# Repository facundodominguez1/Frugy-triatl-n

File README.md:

# Robot Triatlon "FRUGY" - Bonaerenses 2025

## Frugy 

Este proyecto robot triatlón fue creado con la intencion de competir en las Bonaerenses 21/08/2025. Que fue llevado por los alumnos de 5°6 Ulises Basabe, Facundo Dominguez, Gonzalo Flores y Ramiro Trejo. A lo largo de varias pruebas realizadas por los mismos.

**Todo este proyecto pudo funcionar gracias a los programas de Arduino Ide para su desarollo de software, KiCad 9.0 para su desarrollo de PCBs, y por ultimo Fusion 360 para su diseño 3D**

## SUMO RC
Esta categoría llamada Sumo RC (Radio Controlado), se basa en quitar del tatami al rival, el cual una persona está encargada de maniobrar al robot.

## VELOCISTA
Por este lado el robot tiene como objetivo completar una pista de carreas de la manera mas rápida y precisa posible, que en esta pista se pueden llegar a incluir obstaculos para dificultar la vuelta

## DESPEJA AREA
Esta rama es cuando el robot tiene que sacar una serie de cubos de una pista de la manera mas eficiente, obteniendo así dsitintos puntajes sin este poder salir de la misma 

## ⚒ LISTA DE COMPONENTES

- 2 Baterias de LiPo 3s 1050 mAh
- 5 Sensores de distancia AD32
- 1 Regleta de sensores QTR8A
- 3 Sensores de piso TCRT5000
- 2 Motores JGA25-370 DE 280RPM
- 2 Drivers TA6586
- 1 Microcontrolador ESP32 de 38 Pines
- 2 Placas de pertinax 10cmX10cm
- 1 Led Neopixel

## FALLAS Y DETALLES 

- En este proyecto hubo muchos problemas con calculo de tiempos
- Desconocimiento para un proyecto tan importante
- No tener muy en cuenta el gasto total del proyecto

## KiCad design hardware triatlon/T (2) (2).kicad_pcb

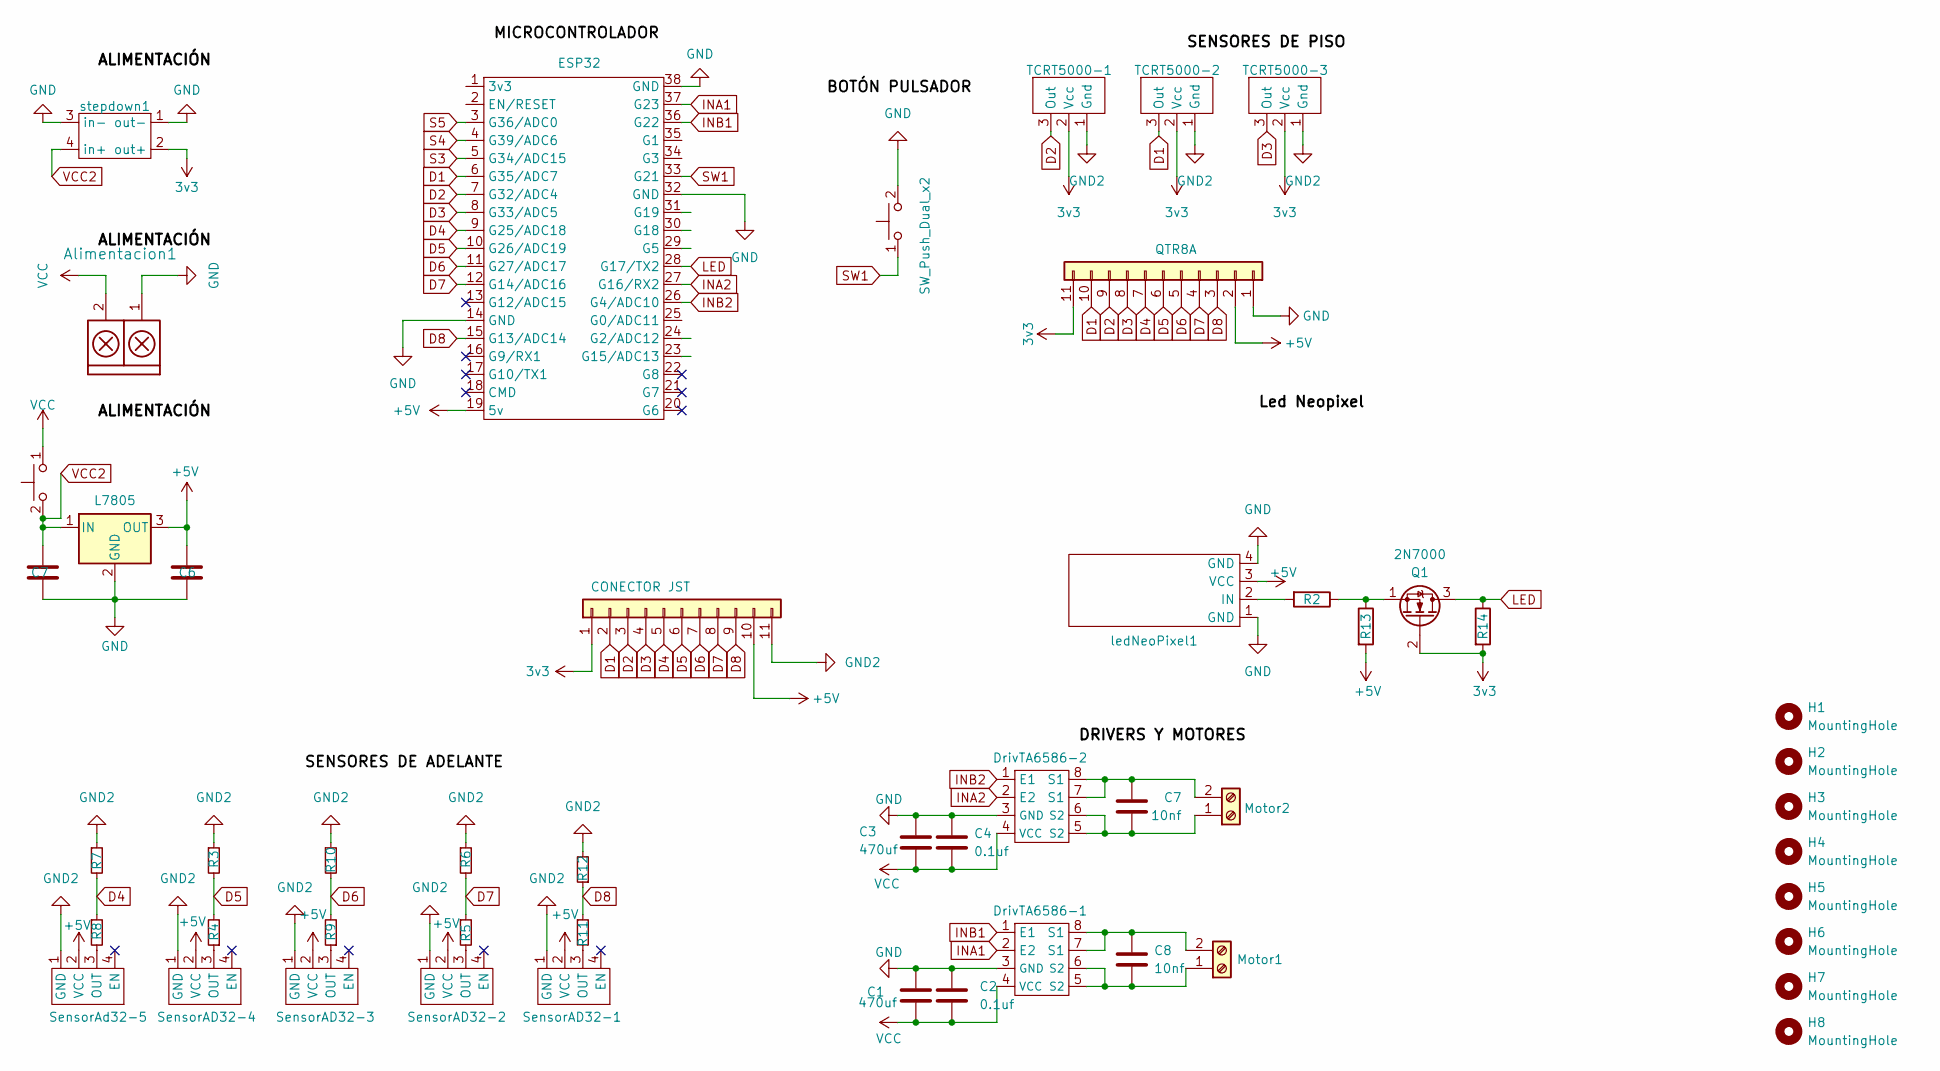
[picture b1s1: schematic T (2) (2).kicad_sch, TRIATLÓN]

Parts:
Alimentacion1: TB_1X2; BORNERA2_AZUL
C1, C3: 470uf; CP_Radial_D8.0mm_P3.80mm
C2, C4: 0.1uf; C_Disc_D5.0mm_W2.5mm_P2.50mm
C5: C7; C_Disc_D5.0mm_W2.5mm_P2.50mm
C6: 0.01uf; C_Disc_D5.0mm_W2.5mm_P2.50mm
C7, C8: 10nf; C_Disc_D5.0mm_W2.5mm_P2.50mm
DrivTA6586-1, DrivTA6586-2: DIP-8_W7.62mm
ESP32: ESP32_T
H1, H2, H3, H4, H5, H6, H7, H8: MountingHole; MountingHole_3.2mm_M3_DIN965
J2: QTR8A; JST_EH_B11B-EH-A_1x11_P2.50mm_Vertical
J3: CONECTOR JST; JST_EH_B11B-EH-A_1x11_P2.50mm_Vertical
Motor1, Motor2: Screw_Terminal_01x02; BORNERA2_AZUL
Q1: 2N7000; TO-92_Wide
R2: 330; R_Axial_DIN0207_L6.3mm_D2.5mm_P7.62mm_Horizontal
R3, R6, R7, R10, R12: 2.2K; R_Axial_DIN0207_L6.3mm_D2.5mm_P7.62mm_Horizontal
R4, R5, R8, R9, R11: 1K; R_Axial_DIN0207_L6.3mm_D2.5mm_P7.62mm_Horizontal
R13, R14: 10K; R_Axial_DIN0207_L6.3mm_D2.5mm_P7.62mm_Horizontal
SensorAD32-1, SensorAD32-2, SensorAD32-3, SensorAD32-4: JST-4V
SensorAd32-5: JST-4V
TCRT5000-1, TCRT5000-2, TCRT5000-3: JST-3V
U10: L7805; TO-220-3_Vertical
boton1: SW_Push_Dual_x2; PinHeader_1x02_P2.54mm_Vertical
boton3: SW_Push_Dual_x2; BORNERA3_AZUL
ledNeoPixel1: PinHeader_1x04_P2.54mm_Vertical
stepdown1: STEPDOWN

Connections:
3v3: J2.11, J3.1, Q1.2 (G), R14.2, TCRT5000-1.2 (Vcc), TCRT5000-2.2 (Vcc), TCRT5000-3.2 (Vcc), stepdown1.2 (out+)
+5V: C6.1, ESP32.19 (5v), J2.2, J3.10, R13.2, SensorAD32-1.2 (VCC), SensorAD32-2.2 (VCC), SensorAD32-3.2 (VCC), SensorAD32-4.2 (VCC), SensorAd32-5.2 (VCC), U10.3 (OUT), ledNeoPixel1.3 (VCC)
D1: ESP32.6 (G35/ADC7), J2.10, J3.2, TCRT5000-2.3 (Out)
D2: ESP32.7 (G32/ADC4), J2.9, J3.3, TCRT5000-1.3 (Out)
D3: ESP32.8 (G33/ADC5), J2.8, J3.4, TCRT5000-3.3 (Out)
D4: ESP32.9 (G25/ADC18), J2.7, J3.5, R7.2, R8.1
D5: ESP32.10 (G26/ADC19), J2.6, J3.6, R3.2, R4.2
D6: ESP32.11 (G27/ADC17), J2.5, J3.7, R9.2, R10.2
D7: ESP32.12 (G14/ADC16), J2.4, J3.8, R5.1, R6.2
D8: ESP32.15 (G13/ADC14), J2.3, J3.9, R11.1, R12.1
GND: Alimentacion1.1, C1.1, C2.1, C3.1, C4.1, C5.2, C6.2, DrivTA6586-1.3 (GND), DrivTA6586-2.3 (GND), ESP32.14 (GND), ESP32.32 (GND), ESP32.38 (GND), J2.1, U10.2 (GND), boton1.2 (D), ledNeoPixel1.1 (GND), ledNeoPixel1.4 (GND), stepdown1.1 (out-), stepdown1.3 (in-)
GND2: J3.11, R3.1, R6.1, R7.1, R10.1, R12.2, SensorAD32-1.1 (GND), SensorAD32-2.1 (GND), SensorAD32-3.1 (GND), SensorAD32-4.1 (GND), SensorAd32-5.1 (GND), TCRT5000-1.1 (Gnd), TCRT5000-2.1 (Gnd), TCRT5000-3.1 (Gnd)
INA1: DrivTA6586-1.2 (E2), ESP32.37 (G23)
INA2: DrivTA6586-2.2 (E2), ESP32.27 (G16/RX2)
INB1: DrivTA6586-1.1 (E1), ESP32.36 (G22)
INB2: DrivTA6586-2.1 (E1), ESP32.26 (G4/ADC10)
LED: ESP32.28 (G17/TX2), Q1.3 (D), R14.1
unnamed: C8.2, DrivTA6586-1.5 (S2), DrivTA6586-1.6 (S2), Motor1.1
unnamed: C8.1, DrivTA6586-1.7 (S1), DrivTA6586-1.8 (S1), Motor1.2
unnamed: C7.2, DrivTA6586-2.5 (S2), DrivTA6586-2.6 (S2), Motor2.1
unnamed: C7.1, DrivTA6586-2.7 (S1), DrivTA6586-2.8 (S1), Motor2.2
unnamed: Q1.1 (S), R2.1, R13.1
unnamed: R11.2, SensorAD32-1.3 (OUT)
unnamed: R5.2, SensorAD32-2.3 (OUT)
unnamed: R9.1, SensorAD32-3.3 (OUT)
unnamed: R4.1, SensorAD32-4.3 (OUT)
unnamed: R8.2, SensorAd32-5.3 (OUT)
unnamed: R2.2, ledNeoPixel1.2 (IN)
S3: ESP32.5 (G34/ADC15)
S4: ESP32.4 (G39/ADC6)
S5: ESP32.3 (G36/ADC0)
SW1: ESP32.33 (G21), boton1.1 (C)
VCC: Alimentacion1.2, C1.2, C2.2, C3.2, C4.2, DrivTA6586-1.4 (VCC), DrivTA6586-2.4 (VCC), boton3.1 (C)
VCC2: C5.1, U10.1 (IN), boton3.2 (D), stepdown1.4 (in+)

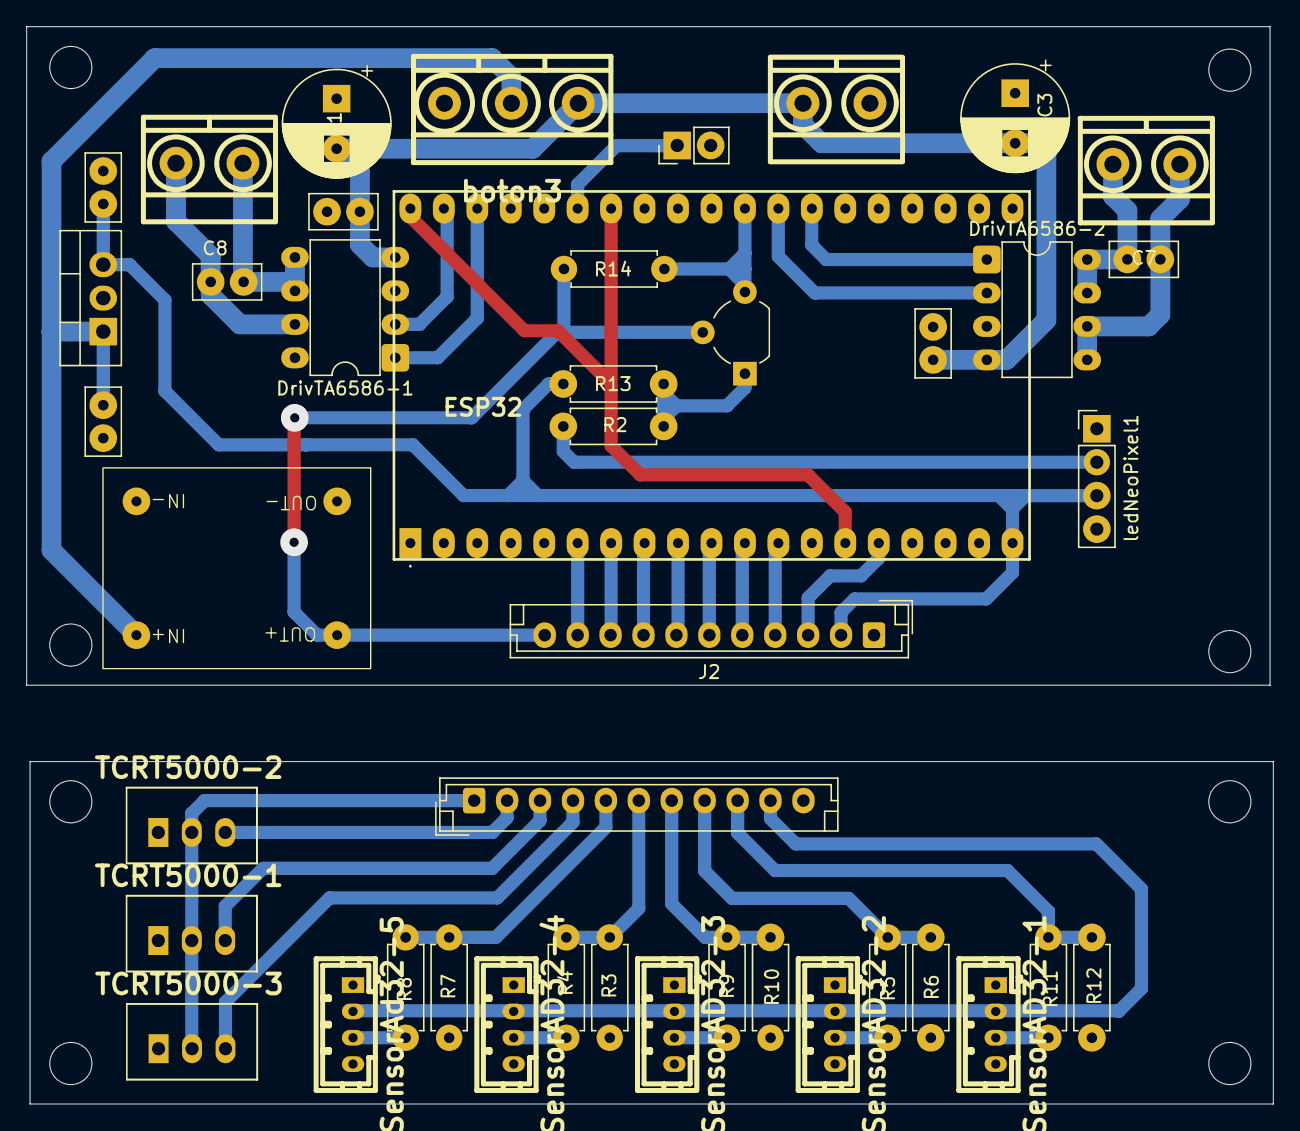
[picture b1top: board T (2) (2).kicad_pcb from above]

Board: 2 copper layers, 94.7 x 81.8 mm, 51 parts (0 on the bottom side), 31 nets.

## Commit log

2025-09-13 sprinter_mode
2025-09-13 search_mode
2025-09-13 despeja_area.ino
2025-09-13 Sumo
2025-09-13 Esquematico
2025-09-13 Diseño placas
2025-09-13 kicad_projects
2025-09-13 Diseños 3D
2025-09-13 Carroceria
2025-09-13 soporte motores
2025-09-15 sprinter_mode_2
2025-09-19 Create sdsds
2025-09-19 Piezas archivos.gcode
2025-09-20 Archivo Fusión 360
2025-09-20 Carrocería Frugy stl
2025-09-20 Carrocería archivo Fusión 360
2025-09-20 Archivos stl
2025-10-02 Add files via upload
    esta placa fue la unica que se usó y que nos dio un fallo de que se quemo la placa
2025-10-02 Create Hardware
2025-10-19 README.md
